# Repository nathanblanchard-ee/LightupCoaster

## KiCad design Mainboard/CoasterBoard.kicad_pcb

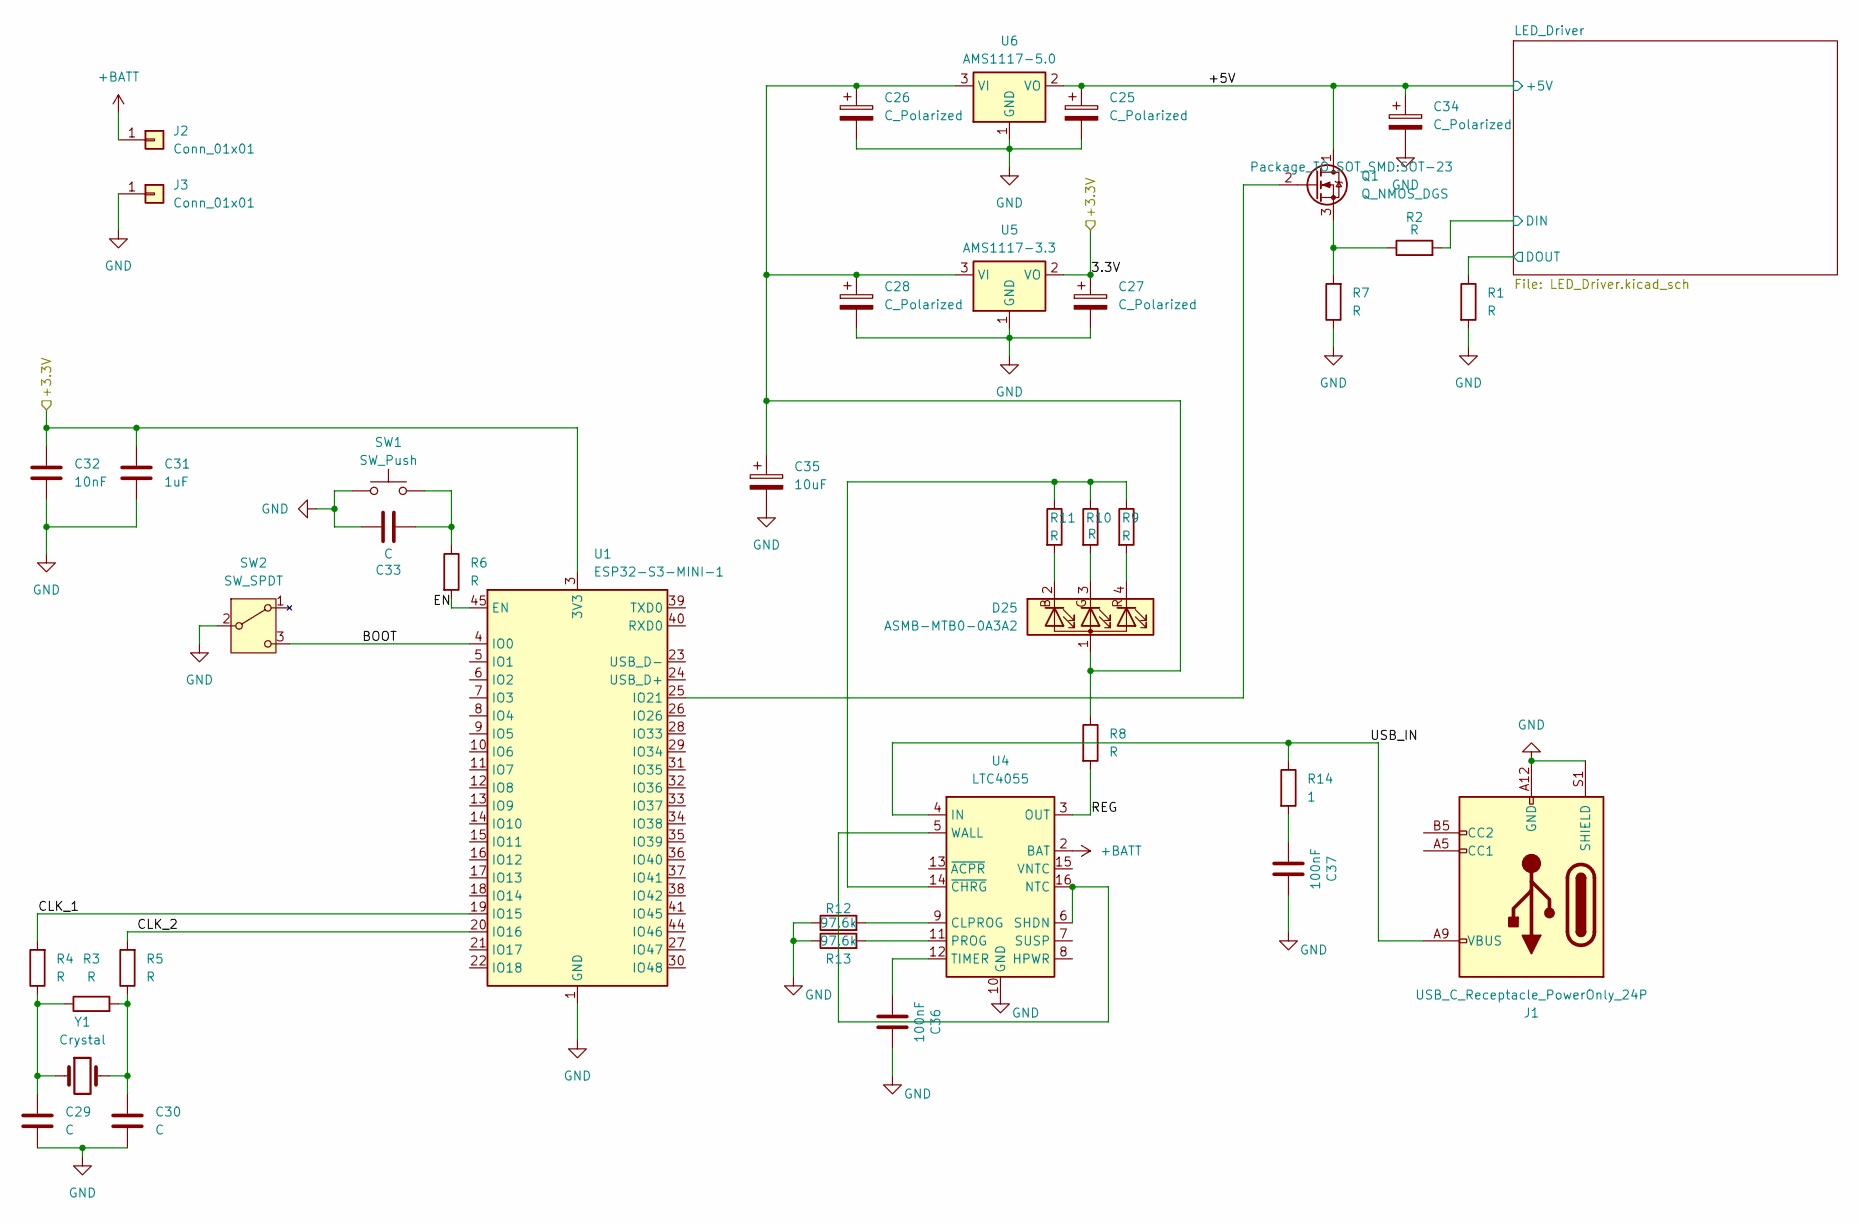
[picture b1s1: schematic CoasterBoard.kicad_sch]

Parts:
C25, C26, C27, C28, C34: C_Polarized; CP_Elec_3x5.4
C29, C30, C33: C; C_0402_1005Metric
C31: 1uF; CP_Elec_3x5.4
C32: 10nF; CP_Elec_3x5.4
C35: 10uF; CP_Elec_3x5.4
C36, C37: 100nF; C_0402_1005Metric
D25: ASMB-MTB0-0A3A2; LED_Avago_PLCC4_3.2x2.8mm_CW
J1: USB_C_Receptacle_PowerOnly_24P; USB_C_Receptacle_Amphenol_12401610E4-2A_CircularHoles
J2, J3: Conn_01x01; TestPoint_Pad_4.0x4.0mm
Q1: Q_NMOS_DGS; SOT-23
R1, R2, R3, R4, R5, R6, R7, R8, R9, R10, R11: R; R_0201_0603Metric
R12, R13: 97.6k; R_0201_0603Metric
R14: 1; R_0201_0603Metric
SW1: SW_Push; SW_SPST_B3U-1000P
SW2: SW_SPDT; SW_DIP_SPSTx01_Slide_6.7x4.1mm_W6.73mm_P2.54mm_LowProfile_J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
U1: ESP32-S3-MINI-1; ESP32-S2-MINI-1
U4: LTC4055; QFN-16-1EP_4x4mm_P0.65mm_EP2.15x2.15mm
U5: AMS1117-3.3; SOT-223-3_TabPin2
U6: AMS1117-5.0; SOT-223-3_TabPin2
Y1: Crystal; Crystal_SMD_Qantek_QC5CB-2Pin_5x3.2mm

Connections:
+BATT: J2.1, U4.2 (BAT)
/+3.3V: C27.1, C31.1, C32.1, U1.3 (3V3), U5.2 (VO)
/LED_Driver/+5V: C25.1, C34.1, Q1.1 (D), U6.2 (VO); also elsewhere on the board
/LED_Driver/DIN: R2.2; also elsewhere on the board
/LED_Driver/DOUT: R1.1; also elsewhere on the board
GND: C25.2, C26.2, C27.2, C28.2, C29.2, C30.2, C31.2, C32.2, C33.1, C34.2, C35.2, C36.1, C37.1, J1.A1 (GND), J1.A12 (GND), J1.B1 (GND), J1.B12 (GND), J1.S1 (SHIELD), J3.1, R1.2, R7.1, R12.1, R13.1, SW1.1, SW2.2 (B), U1.1 (GND), U1.2 (GND), U1.42 (GND), U1.43 (GND), U1.46 (GND), U1.47 (GND), U1.48 (GND), U1.49 (GND), U1.50 (GND), U1.51 (GND), U1.52 (GND), U1.53 (GND), U1.54 (GND), U1.55 (GND), U1.56 (GND), U1.57 (GND), U1.58 (GND), U1.59 (GND), U1.60 (GND), U1.61 (GND), U1.62 (GND), U1.63 (GND), U1.64 (GND), U1.65 (GND), U4.10 (GND), U4.17 (GND), U5.1 (GND), U6.1 (GND); also elsewhere on the board
unnamed: C29.1, R3.1, R4.1, Y1.1
unnamed: C30.1, R3.2, R5.1, Y1.2
unnamed: C33.2, R6.1, SW1.2
unnamed: C37.2, R14.2
unnamed: C26.1, C28.1, C35.1, D25.1 (A), R8.1, U5.3 (VI), U6.3 (VI)
unnamed: D25.2 (BK), R11.2
unnamed: D25.3 (GK), R10.2
unnamed: D25.4 (RK), R9.2
unnamed: J1.A4 (VBUS), J1.A9 (VBUS), J1.B4 (VBUS), J1.B9 (VBUS), R14.1, U4.1 (IN), U4.4 (IN)
unnamed: Q1.2 (G), U1.25 (IO21)
unnamed: Q1.3 (S), R2.1, R7.2
unnamed: SW2.3 (C), U1.4 (IO0)
unnamed: R6.2, U1.45 (EN)
unnamed: R4.2, U1.19 (IO15)
unnamed: R5.2, U1.20 (IO16)
unnamed: R12.2, U4.9 (CLPROG)
unnamed: U4.5 (WALL), U4.6 (SHDN), U4.16 (NTC)
unnamed: R8.2, U4.3 (OUT)
unnamed: R13.2, U4.11 (PROG)
unnamed: C36.2, U4.12 (TIMER)
unnamed: R9.1, R10.1, R11.1, U4.14 (~CHRG)

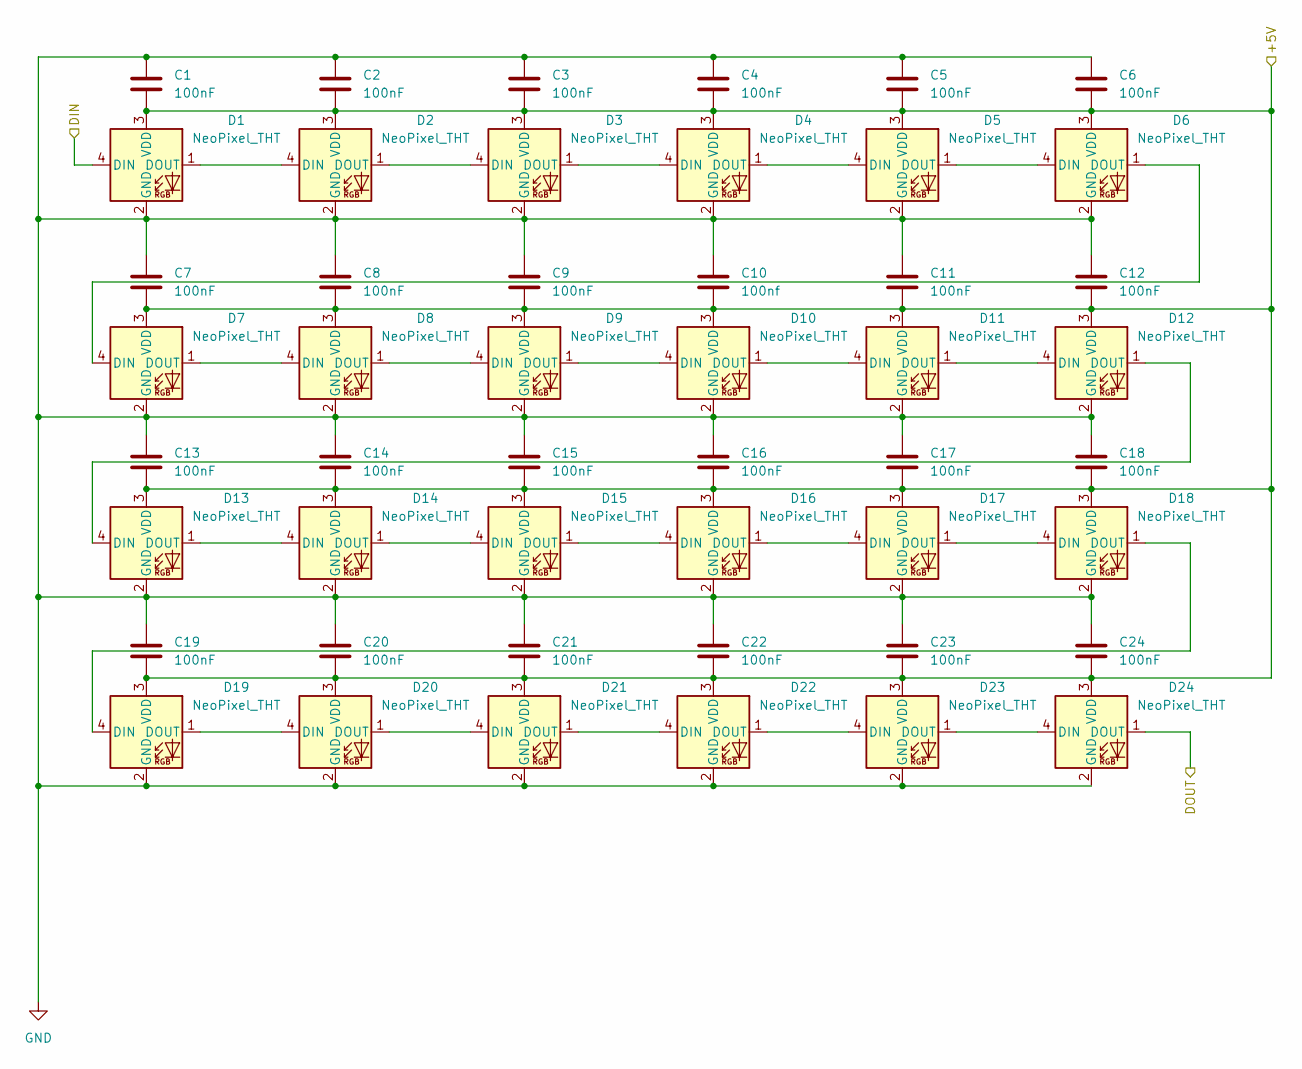
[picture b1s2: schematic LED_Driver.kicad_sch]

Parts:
C1, C2, C3, C4, C5, C6, C7, C8, C9, C11, C12, C13, C14, C15, C16, C17, C18, C19, C20, C21, C22, C23, C24: 100nF; C_0402_1005Metric
C10: 100nf; C_0402_1005Metric
D1, D2, D3, D4, D5, D6, D7, D8, D9, D10, D11, D12, D13, D14, D15, D16, D17, D18, D19, D20, D21, D22, D23, D24: NeoPixel_THT; LED_SK6812_EC15_1.5x1.5mm

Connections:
/LED_Driver/+5V: C1.2, C2.2, C3.2, C4.2, C5.2, C6.2, C7.2, C8.2, C9.2, C10.2, C11.2, C12.2, C13.2, C14.2, C15.2, C16.2, C17.2, C18.2, C19.2, C20.2, C21.2, C22.2, C23.2, C24.2, D1.3 (VDD), D2.3 (VDD), D3.3 (VDD), D4.3 (VDD), D5.3 (VDD), D6.3 (VDD), D7.3 (VDD), D8.3 (VDD), D9.3 (VDD), D10.3 (VDD), D11.3 (VDD), D12.3 (VDD), D13.3 (VDD), D14.3 (VDD), D15.3 (VDD), D16.3 (VDD), D17.3 (VDD), D18.3 (VDD), D19.3 (VDD), D20.3 (VDD), D21.3 (VDD), D22.3 (VDD), D23.3 (VDD), D24.3 (VDD); also elsewhere on the board
/LED_Driver/DIN: D1.4 (DIN); also elsewhere on the board
/LED_Driver/DOUT: D24.1 (DOUT); also elsewhere on the board
GND: C1.1, C2.1, C3.1, C4.1, C5.1, C6.1, C7.1, C8.1, C9.1, C10.1, C11.1, C12.1, C13.1, C14.1, C15.1, C16.1, C17.1, C18.1, C19.1, C20.1, C21.1, C22.1, C23.1, C24.1, D1.2 (GND), D2.2 (GND), D3.2 (GND), D4.2 (GND), D5.2 (GND), D6.2 (GND), D7.2 (GND), D8.2 (GND), D9.2 (GND), D10.2 (GND), D11.2 (GND), D12.2 (GND), D13.2 (GND), D14.2 (GND), D15.2 (GND), D16.2 (GND), D17.2 (GND), D18.2 (GND), D19.2 (GND), D20.2 (GND), D21.2 (GND), D22.2 (GND), D23.2 (GND), D24.2 (GND); also elsewhere on the board
unnamed: D1.1 (DOUT), D2.4 (DIN)
unnamed: D2.1 (DOUT), D3.4 (DIN)
unnamed: D3.1 (DOUT), D4.4 (DIN)
unnamed: D4.1 (DOUT), D5.4 (DIN)
unnamed: D5.1 (DOUT), D6.4 (DIN)
unnamed: D6.1 (DOUT), D7.4 (DIN)
unnamed: D7.1 (DOUT), D8.4 (DIN)
unnamed: D8.1 (DOUT), D9.4 (DIN)
unnamed: D9.1 (DOUT), D10.4 (DIN)
unnamed: D10.1 (DOUT), D11.4 (DIN)
unnamed: D11.1 (DOUT), D12.4 (DIN)
unnamed: D12.1 (DOUT), D13.4 (DIN)
unnamed: D13.1 (DOUT), D14.4 (DIN)
unnamed: D14.1 (DOUT), D15.4 (DIN)
unnamed: D15.1 (DOUT), D16.4 (DIN)
unnamed: D16.1 (DOUT), D17.4 (DIN)
unnamed: D17.1 (DOUT), D18.4 (DIN)
unnamed: D18.1 (DOUT), D19.4 (DIN)
unnamed: D19.1 (DOUT), D20.4 (DIN)
unnamed: D20.1 (DOUT), D21.4 (DIN)
unnamed: D21.1 (DOUT), D22.4 (DIN)
unnamed: D22.1 (DOUT), D23.4 (DIN)
unnamed: D23.1 (DOUT), D24.4 (DIN)

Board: 2 copper layers, 87 parts (48 on the bottom side), 49 nets, no tracks yet.

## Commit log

2025-09-10 Add KiCAD files
